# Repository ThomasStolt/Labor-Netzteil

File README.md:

# Labor-Netzteil

Sooo, der Spaß hier soll ein Steam-Punk-Labornetzteil werden. Dazu nehme ich 2 x den Bausatz von Banggood (30V/3A). Kostet nix, reicht aber völlig aus.

# Zutaten
* Der "Hiland" 30V / 3A Power Supply Bausatz aus dem fernöstlichen Versand
* https://youtu.be/GyKeNLSQvXk - der Bausatz selbst
* https://youtu.be/txPFAZrlzXQ - Schwellspannungsschalter, die Idee ist super, zur Realisierung werde ich hier allerdings zwei ADC EingÃ¤nge eines ESP32 nutzn
* https://youtu.be/yiRMvMb5ZxQ - Teil 2 des Netzteilprojektes ... so Ãhnlich habe ich das auch vor, nur schöner :)Ä
* 2 x Ringkerntrafos (RKT 12012, https://www.reichelt.de/ringkerntrafo-120-va-2x-12-v-2x-5-0-a-rkt-12012-p15262.html?&nbc=1)
* 4 x vernünftige Präzisionspotis, 10-Gang (534-10k) von Vishay (534B1103JC)
* Potiknöpfe von Marshall-Verstärkern :)
* Ein ausgedienter Intel-Prozessorlüfter
* Ein ESP32 DevKit C V4 zum temperaturabhängigen Lüftersteuerung, als Schwellwertumschaltung für den Trafo sowie zum Betrieb der NeoPixel für die Innenbeleuchtung
* Zwei digitale Kombi-Anzeigen V und A, auch aus dem fernen Osten
* Eventuell kommt noch ein OLED für diverse Info's hinzu, noch nicht klar
* Eine alte Schatzkiste als Steam-Punk-Gehäuse

# Log
## 11.05.2025
Nach langer Zeit endlich mal wieder etwas Zeit in das Projekt stecken. Letzt Erkenntnisse waren, das die Schaltung so nicht funktioniert. Schwierig zu erklären, aber die Idee aus dem Trafo 12V und 5V abzugreifen und damit die Logik-Schaltung zu versorgen hat einfach nicht funktioniert. Also, neuer Ansatz, es kommt ein kleines Netzteil 5V/4A zum Einsatz. Darüber werden dann der Lüfter als auch die Neopixel versorgt. 
Ich habe mich jetzt für andere Display Module entschieden, und zwar die ST7789v2, mit abgerundeten Ecken. Die sehen sehr schick aus und ich habe in einem andere (kleinen) Projekt gelernt, wie man damit umgeht. Sehen echt stark aus.
Ausserdem kommt noch ein Verstärkermodul (MAX98735A) hinein - das Singende Klingende Labornetzteil ;)

Neue Platine ist auch entworfen. Mal schauen, wie viele Fehler da jetzt drin sind ;)

## 10.02.2024
Das PCB ist gekommen und scheint soweit zu passen. Ein paar kleinere Sachen habe ich vergessen (z.B. einen Anschluss für die Anzeigen), aber das ist halb so schlimmt. Zuerst hatte ich die Anzeigen falsch angeschlossen und sie haben unplausible Werte angezeigt. Nach etwas Googlen war dann aber klar, wie sie anzuschliessen sind.
Grundsätzlich laufen jetzt die beiden Netzteile, im Moment noch bis 15V, da die Umschaultung auf 24V AC noch fehlt. Aber sieht schon ganz gut aus alles. :)

## 29.01.2024
Endlich komme ich mal wieder hierzu. Ich habe jetzt einfach mal die Leiterplatten so bestellt. Ob das alles so in die Kiste reinpast, die ich dafür gehot habe, ist fraglich. Es bleibt spannend! :)

## 24.03.2020
Endlich ist das Relais-Modul angekommen. Wenn ich solche Module bekomme, dann entlöte ich generell die Anschlüsse und baue mir einen entsprechenden Footprint in KiCad, sdass man das Modul direkt auf die Hauptplatine stecken und verlöten kann.

Ich kann die Leiterplatte allerdings noch gar nicht fertigstellen, da ich noch nicht weiss, wieviel und welchen Platz ich im Gehäuse haben werde. Momentan ist die Platine ja fast quadratisch, kann durchaus sein, dass ich sie wegen Platzmangel länglich machen muss. Dazu muss ich jetzt erst noch warten müssen, bis die richtigen Kühlkörper ankommen. Ich hatte zwar welche bestellt, die sind mir aber zu klein. Diese sollten Morgen, spätestens Übermorgen ankommen.

Auch die Marshall Knöpfe sind gekommen ... und sehen seeeeeeeehr gut aus :)

## 23.03.20:
Oh man, jetzt hätte ich beinahe den Vorwiderstand für die NeoPixel vergessen. Ich habe auch gleich noch einen Elko direkt am Anschluß für die NeoPixel platziert, nach 'best practice'.

Ich habe auch gleich noch einen Stützkondensator (470uF/25V) fÃ¼r den ESP32 vorgesehen ... man weiß ja nie!
## 22.03.20:
Leiterplatte weitergemacht. Es ist jetzt das Relais-Modul drauf (Größe ist exakt, die Pins sind noch geschätzt, bis ich das tatsächliche Modul in der Hand habe). Pro Tip: Leiterplatten immer erst designen, wenn du alle Teile physisch auf deinem Tisch liegen hast!

Zusätzlich sind jetzt noch 2 Spannungsteiler drauf. Der Plan ist damit die eingestellte Ausgangsspannung zu messen um bei > 14 Volt den Eingang mit 24V AC zu versorgen, ansonsten 12V AC. Damit sollte die abzuführende Wärme verringert werden (die Idee vom Bitbastelei Video).

Auch sind Anschlüsse drauf für den Temperaturfühler (DS18B20), den Lüfter und die NeoPixel.
## 21.03.20: 
...grad gemerkt, dass es einfacher ist ein fertiges 2-fach Relais-Modul in Asien zu bestellen, als sich die Schaltung selbst zusammenzustellen. Ist unterwegs...
## 21.03.20: 
...auch zum Glück grad gemerkt, dass diese Relais-Module mit 5V betrieben werden, aber auch 5V Eingangssignal benötigen, um zu schalten. Naja, damit habe ich Erfahrung, es kommt also noch ein 74HCT245 hinzu, der zuverlässig als Level-Shifter fungiert.
## 21.3.20.: 
Damit das richtig 'punk-ed' (im SteamPunk-Gehäuse) werde ich ein paar Neo-Pixel in das Gehäuse bauen, die bei Betrieb dann ordentlich Lichteffekte machen können, zu sehen dann durch die Luftein- und -austrittslöcher und eventuelle ritzen :) Dann kann der Level-Shifter gleich helfen beim Betrieb der Neo-Pixel (cool wäre ja auch noch ein Smoke-Generator - aber dass ist dann wohl doch overkill). Aber ein Lautsprecher mit Dampfmaschinengeräusch? Wie geil wäre dass denn? :)
## 20.03.20: 
Ganz zunächst habe ich festgestellt, dass meine geplanten Kühlkörper deutlich zu klein waren. 1A und 1V über einem Lastwidersand haben die Kühlkörper innerhalb von 20 Sekunden auf 80°C gebracht. Also gleich einmal neue bestellt, die sind unterwegs in der Post.

# Top Notch Solution Design vom hochbezahlten Profi! :)

# Status
* Leiterplatte ist im Entwurf, zur Aufnahme der Relais, ESP32 und der Stromversorgung (12V/5V) für den Lüfter und den ESP32

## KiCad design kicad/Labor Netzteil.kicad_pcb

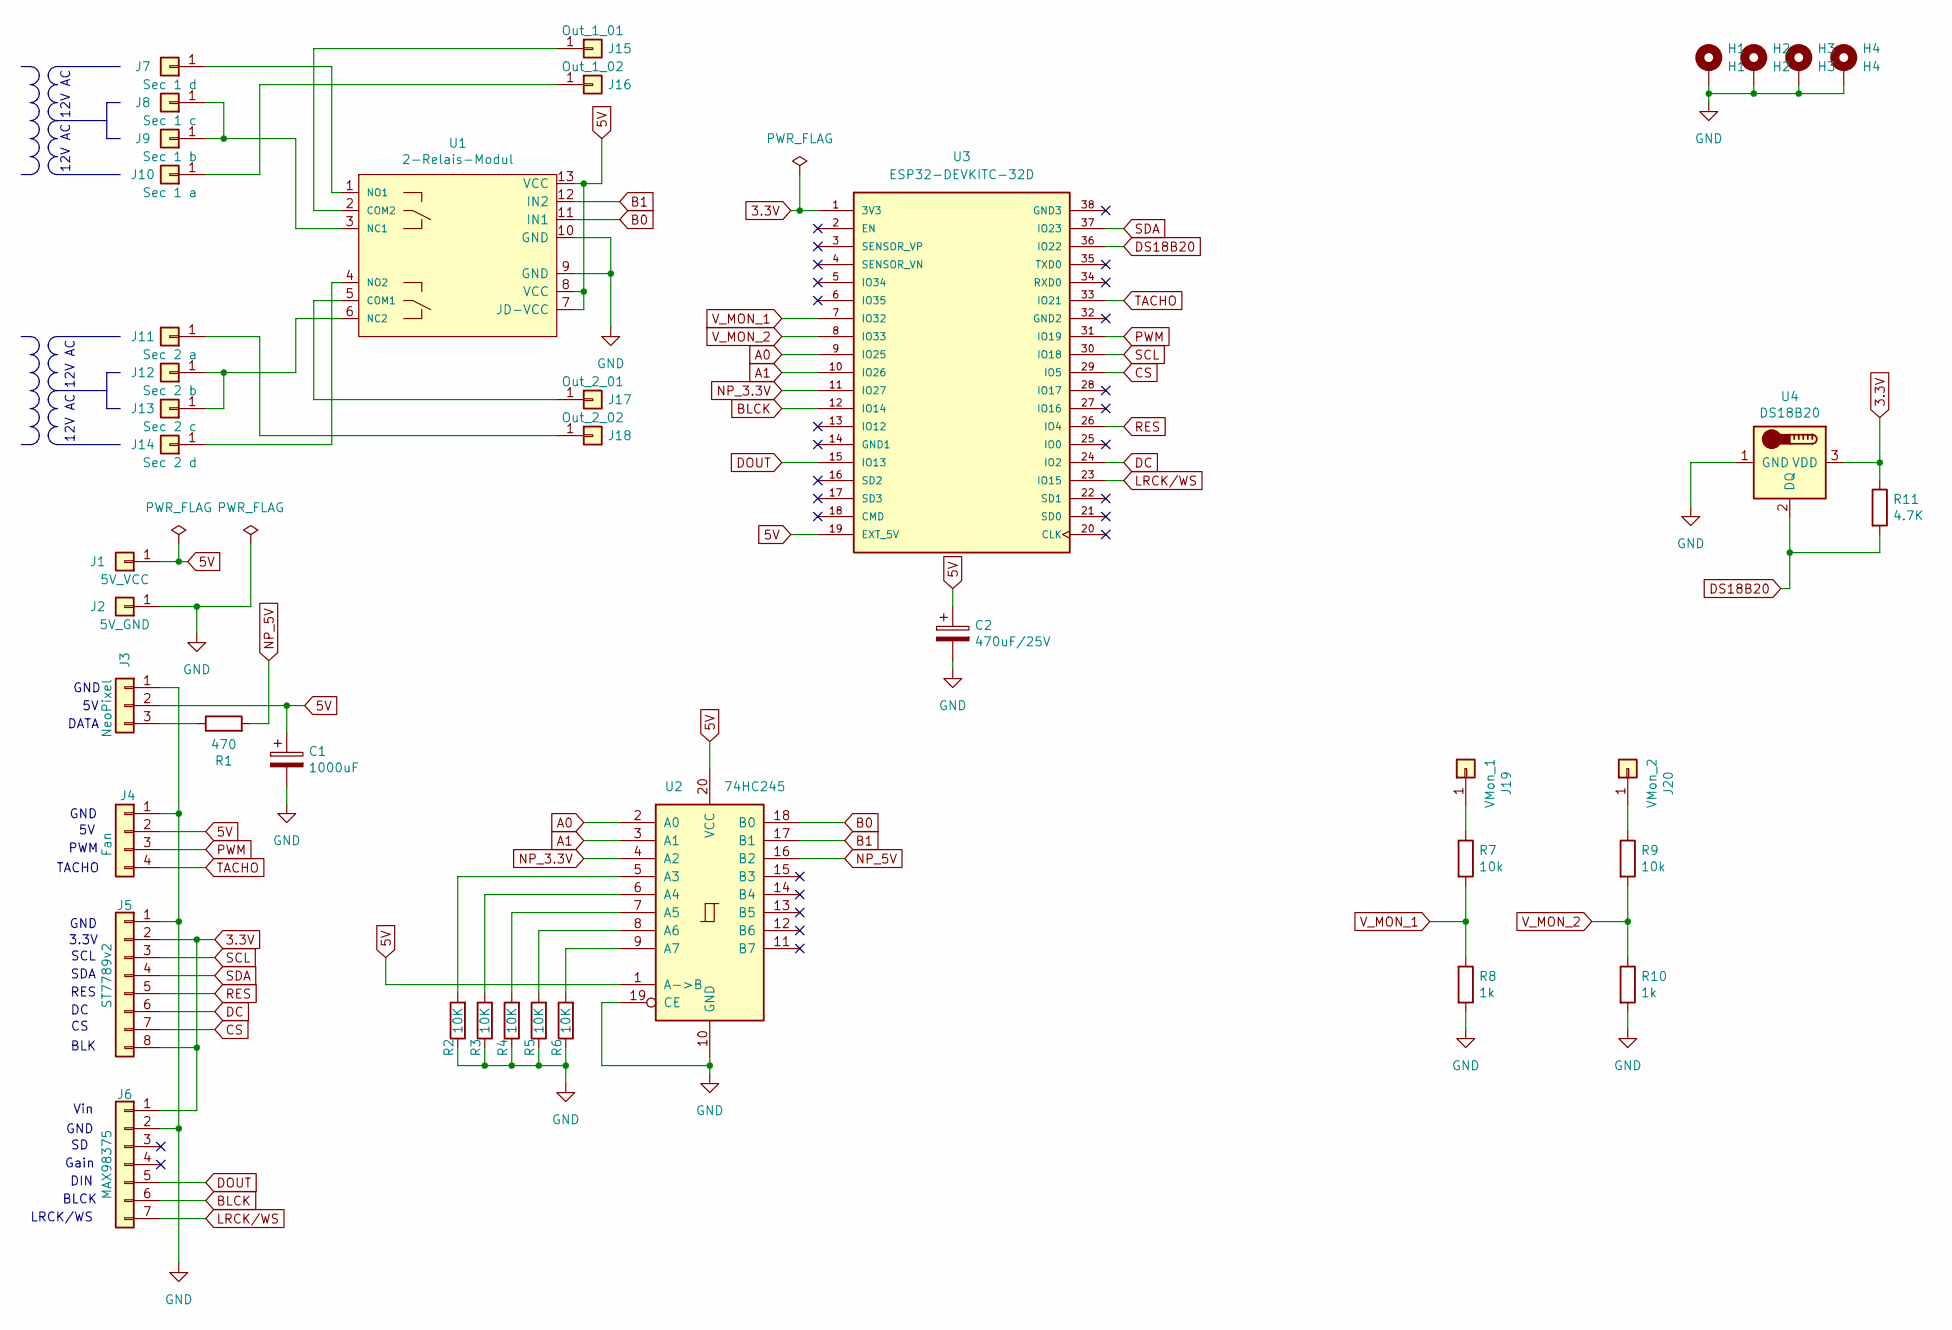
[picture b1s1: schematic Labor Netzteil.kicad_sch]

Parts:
C1: 1000uF; CP_Radial_D8.0mm_P5.00mm
C2: 470uF/25V; CP_Radial_D8.0mm_P3.50mm
H1: H1; MountingHole_3.2mm_M3_Pad_Via
H2: H2; MountingHole_3.2mm_M3_Pad_Via
H3: H3; MountingHole_3.2mm_M3_Pad_Via
H4: H4; MountingHole_3.2mm_M3_Pad_Via
J1: 5V_VCC; Pin_D1.3mm_L11.0mm_LooseFit
J2: 5V_GND; Pin_D1.3mm_L11.0mm_LooseFit
J3: NeoPixel; JST_XH_B3B-XH-A_1x03_P2.50mm_Vertical
J4: Fan; JST_XH_B4B-XH-A_1x04_P2.50mm_Vertical
J5: ST7789v2; JST_XH_B8B-XH-A_1x08_P2.50mm_Vertical
J6: MAX98375; JST_XH_B7B-XH-A_1x07_P2.50mm_Vertical
J7: Sec 1 d; Pin_D1.3mm_L11.0mm_LooseFit
J8: Sec 1 c; Pin_D1.3mm_L11.0mm_LooseFit
J9: Sec 1 b; Pin_D1.3mm_L11.0mm_LooseFit
J10: Sec 1 a; Pin_D1.3mm_L11.0mm_LooseFit
J11: Sec 2 a; Pin_D1.3mm_L11.0mm_LooseFit
J12: Sec 2 b; Pin_D1.3mm_L11.0mm_LooseFit
J13: Sec 2 c; Pin_D1.3mm_L11.0mm_LooseFit
J14: Sec 2 d; Pin_D1.3mm_L11.0mm_LooseFit
J15: Out_1_01; Pin_D1.3mm_L11.0mm_LooseFit
J16: Out_1_02; Pin_D1.3mm_L11.0mm_LooseFit
J17: Out_2_01; Pin_D1.3mm_L11.0mm_LooseFit
J18: Out_2_02; Pin_D1.3mm_L11.0mm_LooseFit
J19: VMon_1; PinHeader_1x01_P1.00mm_Vertical
J20: VMon_2; PinHeader_1x01_P1.00mm_Vertical
R1: 470; R_Axial_DIN0204_L3.6mm_D1.6mm_P7.62mm_Horizontal
R2, R3, R4, R5, R6: 10K; R_Axial_DIN0204_L3.6mm_D1.6mm_P7.62mm_Horizontal
R7, R9: 10k; R_Axial_DIN0204_L3.6mm_D1.6mm_P7.62mm_Horizontal
R8, R10: 1k; R_Axial_DIN0204_L3.6mm_D1.6mm_P7.62mm_Horizontal
R11: 4.7K; R_Axial_DIN0204_L3.6mm_D1.6mm_P7.62mm_Horizontal
U1: 2-Relais-Modul; 2-way-relais-module
U2: 74HC245; DIP-20_W7.62mm_LongPads
U3: ESP32-DEVKITC-32D; ESP32-DevKitC-V4-b; PARTREV V4
U4: DS18B20; TO-92_Inline

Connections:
3.3V: J5.2, J5.8, J6.1, R11.1, U3.1 (3V3), U4.3 (VDD)
5V: C1.1, C2.1, J1.1, J3.2, J4.2, U1.7 (JD-VCC), U1.8 (VCC), U1.13 (VCC), U2.1 (A->B), U2.20 (VCC), U3.19 (EXT_5V)
A0: U2.2 (A0), U3.9 (IO25)
A1: U2.3 (A1), U3.10 (IO26)
B0: U1.11 (IN1), U2.18 (B0)
B1: U1.12 (IN2), U2.17 (B1)
BLCK: J6.6, U3.12 (IO14)
CS: J5.7, U3.29 (IO5)
DC: J5.6, U3.24 (IO2)
DOUT: J6.5, U3.15 (IO13)
DS18B20: R11.2, U3.36 (IO22), U4.2 (DQ)
GND: C1.2, C2.2, H1.1, H2.1, H3.1, H4.1, J2.1, J3.1, J4.1, J5.1, J6.2, R2.1, R3.1, R4.1, R5.1, R6.1, R8.2, R10.2, U1.9 (GND), U1.10 (GND), U2.10 (GND), U2.19 (CE), U4.1 (GND)
LRCK/WS: J6.7, U3.23 (IO15)
NP_3.3V: U2.4 (A2), U3.11 (IO27)
NP_5V: R1.2, U2.16 (B2)
unnamed: J3.3, R1.1
unnamed: J7.1, U1.1 (NO1)
unnamed: J8.1, J9.1, U1.3 (NC1)
unnamed: J10.1, J16.1
unnamed: J11.1, J18.1
unnamed: J12.1, J13.1, U1.6 (NC2)
unnamed: J14.1, U1.4 (NO2)
unnamed: J15.1, U1.2 (COM2)
unnamed: J17.1, U1.5 (COM1)
unnamed: J19.1, R7.1
unnamed: J20.1, R9.1
unnamed: R2.2, U2.5 (A3)
unnamed: R3.2, U2.6 (A4)
unnamed: R4.2, U2.7 (A5)
unnamed: R5.2, U2.8 (A6)
unnamed: R6.2, U2.9 (A7)
PWM: J4.3, U3.31 (IO19)
RES: J5.5, U3.26 (IO4)
SCL: J5.3, U3.30 (IO18)
SDA: J5.4, U3.37 (IO23)
TACHO: J4.4, U3.33 (IO21)
V_MON_1: R7.2, R8.1, U3.7 (IO32)
V_MON_2: R9.2, R10.1, U3.8 (IO33)

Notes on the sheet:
GND
RES
PWM
TACHO
12V AC
DIN
3.3V
SCL
DATA
Vin
BLK
LRCK/WS
SDA
Gain
BLCK

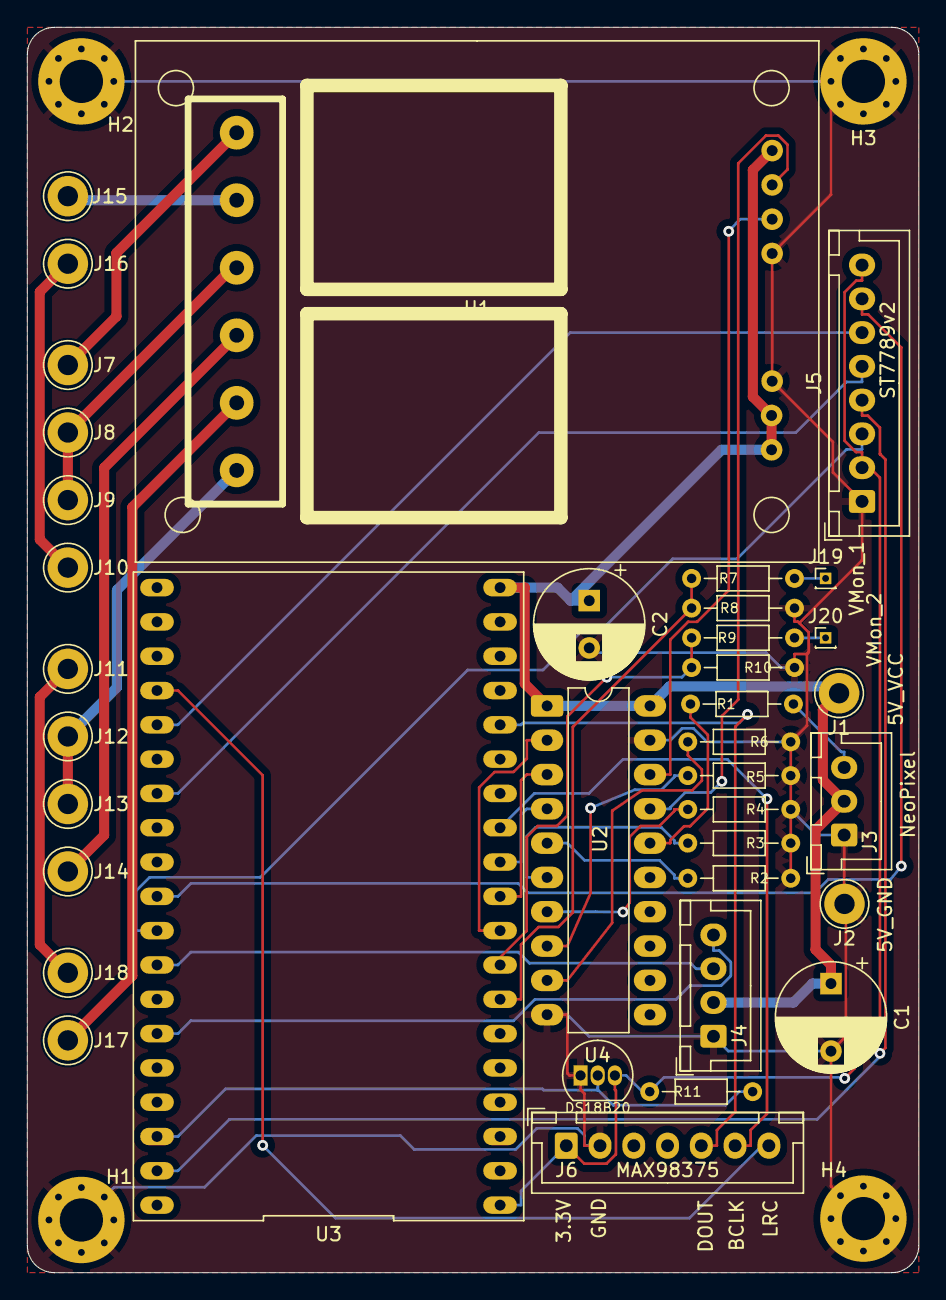
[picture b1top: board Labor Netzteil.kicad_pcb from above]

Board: 2 copper layers, 66.0 x 92.2 mm, 41 parts (0 on the bottom side), 38 nets.

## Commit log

2020-03-20 Neuigkeiten
2020-03-20 Changed location of files
2020-03-20 Some deletions
2020-03-20 Neue Infos, brandheiss
2020-03-21 Coole Bilder
2020-03-21 Diverse Änderungen
2020-03-21 Relais Modul und Level Shifter hinzugefügt
2020-03-22 Leiterplatte im Prinzip fertig
2020-03-22 neues
2020-03-23 Leiterplatte Verbesserungen
2020-03-24 aktuellste Lieferungen und Anpassungen
2024-01-28 added datasheet for tranformer 2 x 12V
2024-01-28 Added PS module datasheet
2024-01-28 Multiple updates
2024-02-10 Added ESP32 DevKit C v4 Datasheet
2024-02-11 some updates
2025-05-11 Neueste Änderungen
2025-05-11 Grundlegende Änderung der Schaltung, siehe README
2025-05-12 Last minor changes to PCB
